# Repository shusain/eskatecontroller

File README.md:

# eskatecontroller

This is a repository for the Arduino code and some CAD files for making PCBs for making a transmitter and receiver
for controlling throttle on an ESC.

Corresponding Thingiverse page http://www.thingiverse.com/thing:1864536

Related part for holding the batteries onto the bottom of the board and for covering the VESC and voltage/amperage display http://www.thingiverse.com/thing:2243206

Other related part remixed VESC case
http://www.thingiverse.com/thing:2263285

Another new part for the board, made an LED headlight/tailight holder that act as risers between the trucks and the board.
https://www.thingiverse.com/thing:2397920

In the Arduino folder there are two sub-folders one for the transmitter/controller and one for the receiver that gets the signal
and sends a PWM signal to an ESC.  The code has comments to explain what the parts do but key points are the transmitter expects
to read an analog signal from a potentiometer on pin A1 and the receiver expects to write a PWM signal to digital pin 5.

The PCB in the Eagle folder and corresponding Eagle files can be used for simplifying and solidifying the connections between
the battery, Arduino and RF module.  There is a PNG in the Images folder that can be printed using a laser printer and transferred
to a copper plate then etched to make a PCB at home, there are lots of instructions online on how to do this but not included
here.  Using the Eagle files one could also export files for a professional fabrication house to make them or forgo them
entirely.

<table>
<tr>
<td style="text-align:center">

</td>
<td style="text-align:center">

</td>
</tr>
<tr>
<td>

</td>
<td>

</td>
</tr>
<tr>
<td>

</td>
<td>

</td>
</tr>
<tr>
<td>

</td>
<td>

</td>
</tr>
</table>

For the EagleCAD PCB the specific parts used are:

  - [Arduino Pro Mini 3.3V](https://www.amazon.com/Diymall-Atmega328-Atmega328p-Arduino-Esp8266/dp/B00NWF2DAU/)
  - [nRF24L01+ 2.4GHz Wireless Transceiver](https://www.amazon.com/gp/product/B00E594ZX0/)

# Assembly Overview

For the PCBs made from PCBway the schematic is slightly different from what you can see from the at home PCB.  The main change is the analog pin for the potentiometer signal into the arduino was going to pin A1 before and has been moved to A2 just because I read up that some things can affect the ADC on A0 and A1 so figured I should just move it to A2 (that same line also connects to D5 which is only used on the receiver side).

There are two, three pin breakouts one marked for ESC and one marked for potentiometer.  For both of these three pin connections the ground is towards the center of the board and the power is through the middle of the three pins and the signal is the pin towards the outside edge of the board.

The ESC middle pin is power in to the RAW pin of the arduino a LiPo is enough to keep it running stable at the 8MHz speed down to below the safe level for the LiPo itself, get ones with built in cut off circuitry to avoid over discharge in the controller, cheap ones available for micro quads in 400 or 800mAh variety, have a 800 mAh one and it lasts a really long time, somewhere around 20mA of draw typically.  The POT middle pin is the 3.3V supply off the arduino.

On the controller/transmitter side you will use the ESC pins to put power into the RAW pin of the Arduino and to connect the ground (pin towards the middle).  The signal pin for the connection marked ESC won't be used in the controller.  The 3 pins for the potentiometer the middle is 3.3V from the arduino (left leg of potentiometer), the pin near the edge is the signal (middle leg of potentiometer typically), and the pin near the center of the PCB is ground (right leg of potentiometer typically). See image above.

Image below shows the way the other PCBs need to attach but in the case of the controller I actually put the arduino on the other side of the board and it is just "upside down" so the reset button and atmel chip are facing "down" at the PCB surface instead of away from it how it's pictured.  In the receiver it is done as pictured.

I rearranged them in the controller just to have a little space on each side vs all the components on one side.

# Assembly Steps
Basically solder the boards together in the arrangement shown.  Good to just solder all the outside rows of arduino pins to get a nice solid connection.  If you'd like you can verify the connections based on the PCB layout below (would share the schematic but sort of useless since I just named all the nets/wires and didn't actually draw connections, it was getting too messy to deal with).

[Note the two inside pins for the ESC and potentiometer appear to not be connected but they are connected to ground]

# Programming

To program the chips you'll need an FTDI breakout adapter that supports 3.3V.  Mine claimed to have 3.3V support but actually still puts 5V+ through the VCC pin and was frying the nrf chips after a few minutes of testing.  After I realized they were over voltage I started using a bench power supply or these 3.3V regulators to step down the 5V power before feeding it into the VCC for the sake of programming.

For the receiver side you can use the Arduino [project file](Arduino/rc_receiver/rc_receiver.ino) from the receiver folder without any modifications really.

For the [transmitter](Arduino/rc_controller/rc_controller.ino) side you'll need to adjust the [high/low](Arduino/rc_controller/rc_controller.ino#L19) values for the controller itself so this sort of needs to be done after assembly (when you actually know the low and high points of the potentiometer).  I had previously programmed it to get that input on startup by swinging it high and low and using those as min and max, but that seems less reliable in the long term and can lead to spinning out your motors when the value isn't set.  Anyhow long story short once assembled you will need to upload the code for the transmitter onto the arduino and then use the serial monitor to see what actual max/min values it reports and adjust the max/min in the code.

Specific steps for programming:

1. Download and install the Arduino IDE if you haven't already.

  https://www.arduino.cc/

2. Download and extract the RF24 library into your arduino libraries folder

  https://github.com/nRF24/RF24

  Extract it to the Arduino folder (mine is in /home/shaun/Arduino/libraries/RF24) do this while the IDE is closed.

3.  Download and extract this repository somewhere.
4.  Open the Arduino/rc_controller/rc_controller.ino file in the Arduino IDE
5.  Change line 5 from

`//#define DEBUGMODE`

to

`#define DEBUGMODE`

This will allow it to print data to the serial line to see what the high and low values should be.

6.  Connect the controller arduino using the FTDI->USB cable to the computer
7.  Upload the code.

8.  Check serial monitor and pull the trigger all the way to its maximum and minimum and note the values at the top and end (they will always be between 0-1024, if they go the wrong direction it doesn't really matter the value mapping will still work, but you can reverse the polarity on the potentiometer to correct that)
9.  Update the code  Lines 19 and 20 have the min and max, just set those to the values you saw and should be good to go (Arduino/rc_controller/rc_controller.ino#L19)
10. Upload the new code (can change line 66 from printing the `sensorValue` to printing the `mappedValue` so you can see that full trigger is 254, full brake is 1 and idle should be near 125).

Should be all set on the controller programming.  The ESC programming is luckily much easier, just get the boards connected, hook up the FTDI open the [receiver.ino](Arduino/rc_receiver/rc_receiver.ino), and upload the receiver code to the board.  When you connect the ESC pins on the receiver side you also won't use the POT breakout pins at all.

If you have issues or these instructions are unclear (cat stuck in toaster) let me know and will see if I can help.

---

Extra note for charging the LiPo can either use a TP4056 or just attach or keep attached the original balance lead.

---

MIT License

Copyright 2017 Shaun Husain

Permission is hereby granted, free of charge, to any person obtaining a copy of this software and associated documentation files (the "Software"), to deal in the Software without restriction, including without limitation the rights to use, copy, modify, merge, publish, distribute, sublicense, and/or sell copies of the Software, and to permit persons to whom the Software is furnished to do so, subject to the following conditions:

The above copyright notice and this permission notice shall be included in all copies or substantial portions of the Software.

THE SOFTWARE IS PROVIDED "AS IS", WITHOUT WARRANTY OF ANY KIND, EXPRESS OR IMPLIED, INCLUDING BUT NOT LIMITED TO THE WARRANTIES OF MERCHANTABILITY, FITNESS FOR A PARTICULAR PURPOSE AND NONINFRINGEMENT. IN NO EVENT SHALL THE AUTHORS OR COPYRIGHT HOLDERS BE LIABLE FOR ANY CLAIM, DAMAGES OR OTHER LIABILITY, WHETHER IN AN ACTION OF CONTRACT, TORT OR OTHERWISE, ARISING FROM, OUT OF OR IN CONNECTION WITH THE SOFTWARE OR THE USE OR OTHER DEALINGS IN THE SOFTWARE.

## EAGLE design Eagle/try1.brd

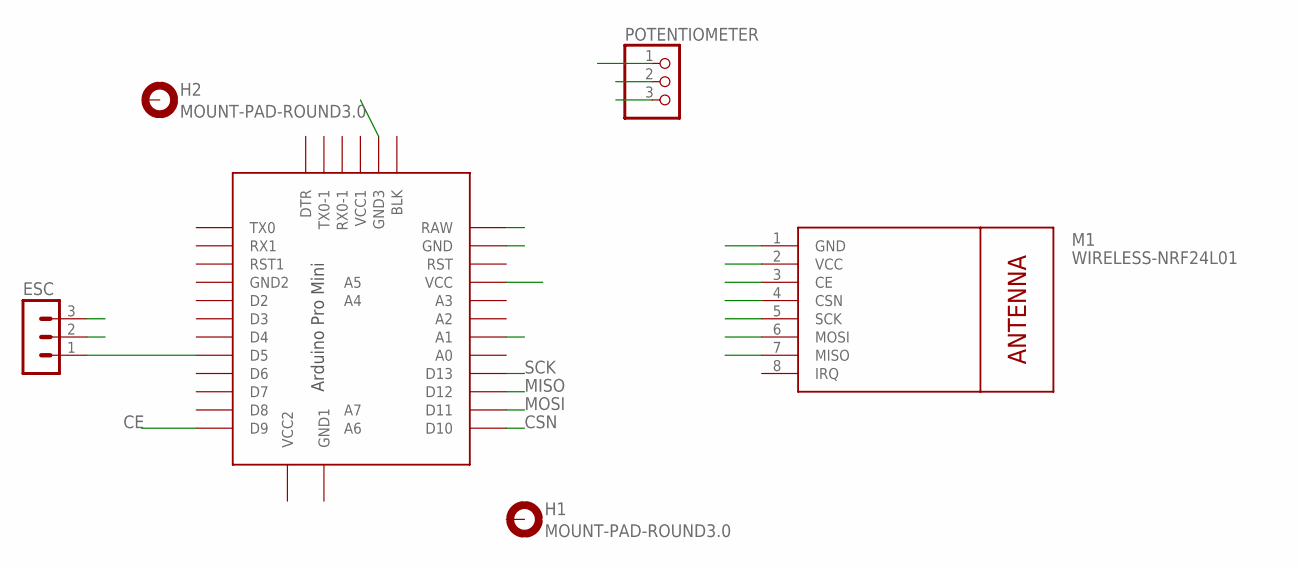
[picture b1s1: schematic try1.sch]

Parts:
ESC: MA03-1
H1, H2: MOUNT-PAD-ROUND3.0; 3,0-PAD
M1: WIRELESS-NRF24L01
POTENTIOMETER: PINHD-1X3; 1X03
U$2: PRO-MINI-33

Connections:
CE: M1.3 (CE), U$2.D9
CSN: M1.4 (CSN), U$2.D10
GND: ESC.3, M1.1 (GND), POTENTIOMETER.3, U$2.GND, U$2.GND3
MISO: M1.7 (MISO), U$2.D12
MOSI: M1.6 (MOSI), U$2.D11
RAW: ESC.2, U$2.RAW
SCK: M1.5 (SCK), U$2.D13
SIG: ESC.1, POTENTIOMETER.1, U$2.A1, U$2.D5
VCC: M1.2 (VCC), POTENTIOMETER.2, U$2.VCC

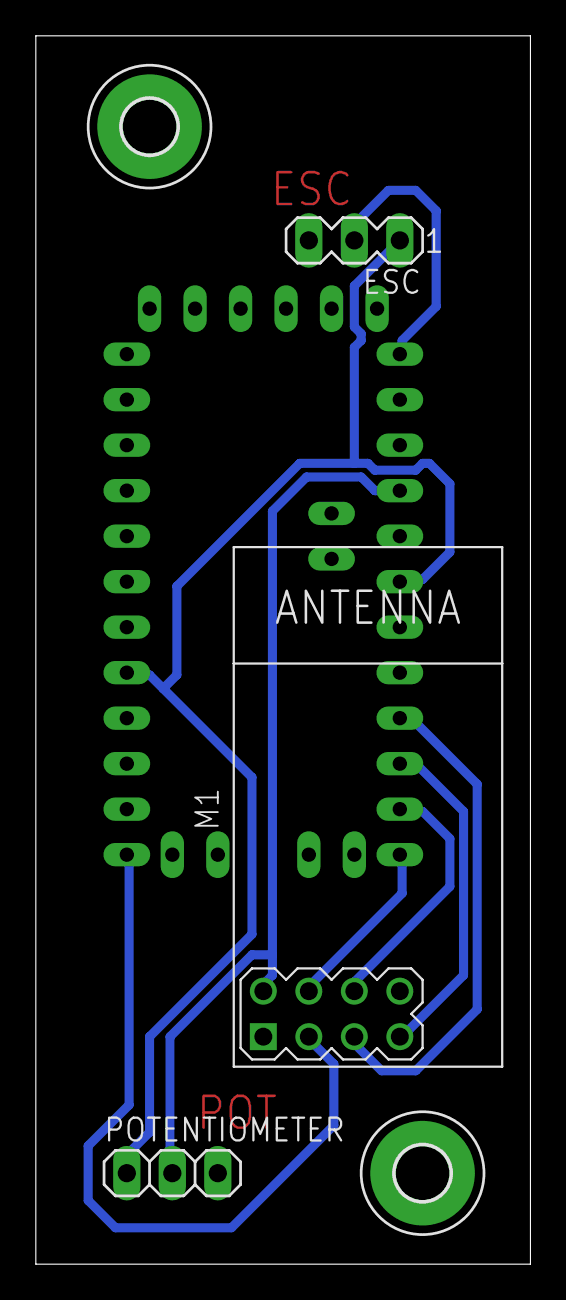
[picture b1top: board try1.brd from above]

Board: 2 copper layers, 27.6 x 68.6 mm, 6 parts (0 on the bottom side), 9 nets.

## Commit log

2016-12-15 Initial Commit Arduino files and Eagle 7.7.0 files
2017-04-09 Fixing so values above 254 are ignored using specific channel for listening.
    Had an issue when the MOSI pin 6 on the nrf module came loose and the receiver goes full throttle, changing to full throttle being 254 so can detect the 255 bad signals if the MOSI pin comes disconne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
2017-04-09 Updating to go from 1 to 254
    Excluding 0 and 255 since these can both come from the radio when there is no signal received (loose connections)
2017-04-15 Updating the PCB design
    Changed the design to fit better in a controller and have a servo style plug so the ground and power can't be reversed only the ground and signal can be reversed which won't damage the circuit. Also 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
2017-04-15 Adding some real photos of the PCB print
    Note there is a blob to connect the ground but this has been corrected in the png exported just wasn't corrected before I etched the board.
2017-04-15 Added 3 pins for potentiometer
    Added another 3 pin connector for the potentiometer to be wired to in the controller/transmitter side. Currently both signals (transmitter or receiver) are on the same line but only one will ever be 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
2017-04-16 Reorganized the photos.
2017-04-16 Updating image paths to show the laser print version and full color version.
2017-04-16 --amend
2017-04-17 Just cleaning up and updating the eagle files.
2017-04-17 Fixing image sizes
2017-04-17 Added image of final PCB in receiver box
2017-04-21 Added some more images and upped the power output on the remote to overcome any interference.
2017-04-21 Added one more picture of the PCB itself from a side view
2017-04-21 just some layout changes to the images
2017-07-12 Updates to the controller code for the new PCBs.
2017-07-12 Updates based on PCBway boards.
2017-07-12 extra note on charging

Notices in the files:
parts and their libraries:
diy-modules: Released under the Creative Commons Attribution 4.0 International License: http://creativecommons.org/licenses/by/4.0
